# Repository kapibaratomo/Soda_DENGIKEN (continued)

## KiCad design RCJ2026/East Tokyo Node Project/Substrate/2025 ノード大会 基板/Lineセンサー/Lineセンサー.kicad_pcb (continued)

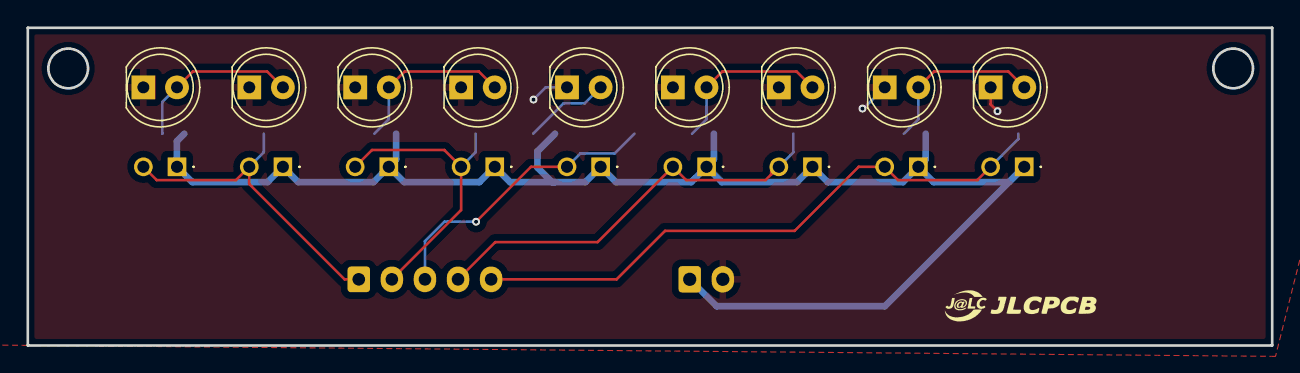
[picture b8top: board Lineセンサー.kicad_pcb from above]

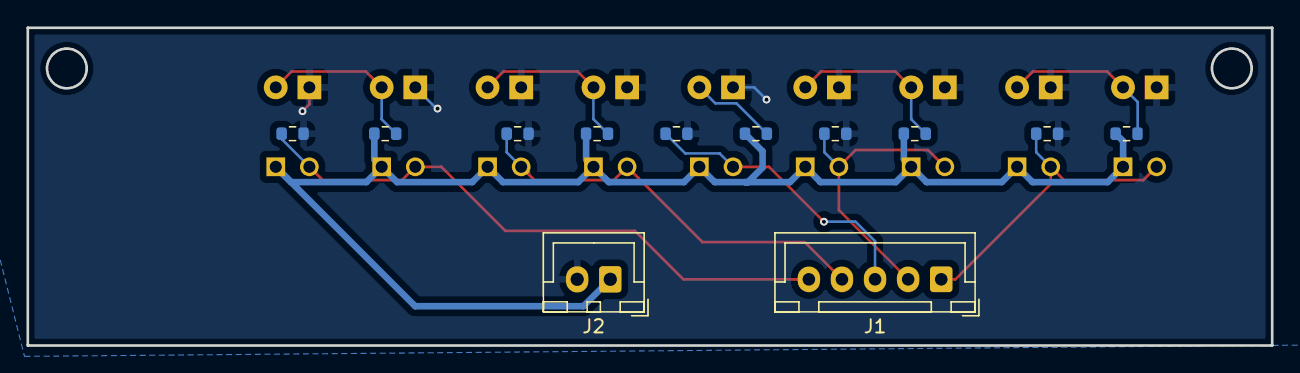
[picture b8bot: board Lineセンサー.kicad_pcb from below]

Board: 2 copper layers, 94.0 x 24.0 mm, 30 parts (12 on the bottom side), 12 nets.
